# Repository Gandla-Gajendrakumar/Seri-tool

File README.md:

# Seri-tool

Low-cost climate monitor for silkworm rearing sheds in India: temperature and humidity
24×7, SMS alerts in Telugu / Kannada / Hindi / English, thermal-printer log, Wi-Fi / 4G upload,
battery backup. Designed and verified in software before any hardware is bought.

## Layout

| Path | Contents |
|---|---|
| `firmware/` | PlatformIO project. `lib/core` = pure, PC-testable logic. `lib/hal` = hardware interfaces. `test/` = unit tests. |
| `sim/wokwi/` | Wokwi virtual hardware: diagram, custom chips (A7670C, printer, SHT31), scenarios. |
| `sim/replay/` | Whole-rearing-cycle replay data and expected outputs. |
| `hardware/kicad/` | Carrier PCB schematic and layout. |
| `hardware/spice/` | ngspice power-stage simulations. |
| `hardware/power_budget/` | Battery-life calculator. |
| `mechanical/cadquery/` | Enclosure and component models. |
| `bom/` | Bill of materials with Indian suppliers. |
| `docs/` | Requirements, decisions, questions, datasheet facts, evidence; **`docs/handoff/` = the hand-off pack.** |
| `hardware/fab/` | PCB fabrication files (Gerbers zip, schematic, assembly drawing, STEP). |
| `firmware/release/` | Flashable firmware binaries with checksums. |
| `tools/` | Helper scripts (`check_toolchain.sh`). |

## Quick check

```
tools/check_toolchain.sh        # exercises every tool; exit code = failures
cd firmware && pio test -e native
```

## Status

| Phase | State | Evidence |
|---|---|---|
| 0 Setup | Approved 2026-11-21 | `tools/check_toolchain.sh`, `docs/requirements.md` |
| 1 Logic | Approved 2026-11-22 | `tools/phase1_gate.sh` → `docs/evidence/phase1-gate.txt` |
| 2 Firmware on virtual hardware | Approved 2026-11-22 (all 8 Wokwi scenarios) | `docs/evidence/phase2-gate.md` |
| 3 Whole-cycle replay | Approved 2026-11-22 | `tools/phase3_gate.sh` → `docs/evidence/phase3-gate.md` |
| 4 Electronics | Approved 2026-11-22 (re-checked after the Keystone 1043 change) | `tools/phase4_gate.sh` → `docs/evidence/phase4-gate.txt`; `docs/hardware/power-architecture.md` |
| 5 BOM | FINAL 2026-11-22 (D-062: in-stock boost module and modem board) | `tools/phase5_gate.sh` → `bom/bom.md`, `docs/evidence/phase5-gate.txt` |
| 6 Enclosure | Approved 2026-11-22 | `tools/phase6_gate.sh` → `docs/evidence/phase6-gate.txt`, renders in `docs/evidence/phase6/` |
| 7 Hand-off pack | Approved 2026-11-22 | `tools/phase7_gate.sh` → `docs/evidence/phase7-gate.txt`; start at `docs/handoff/README.md` |

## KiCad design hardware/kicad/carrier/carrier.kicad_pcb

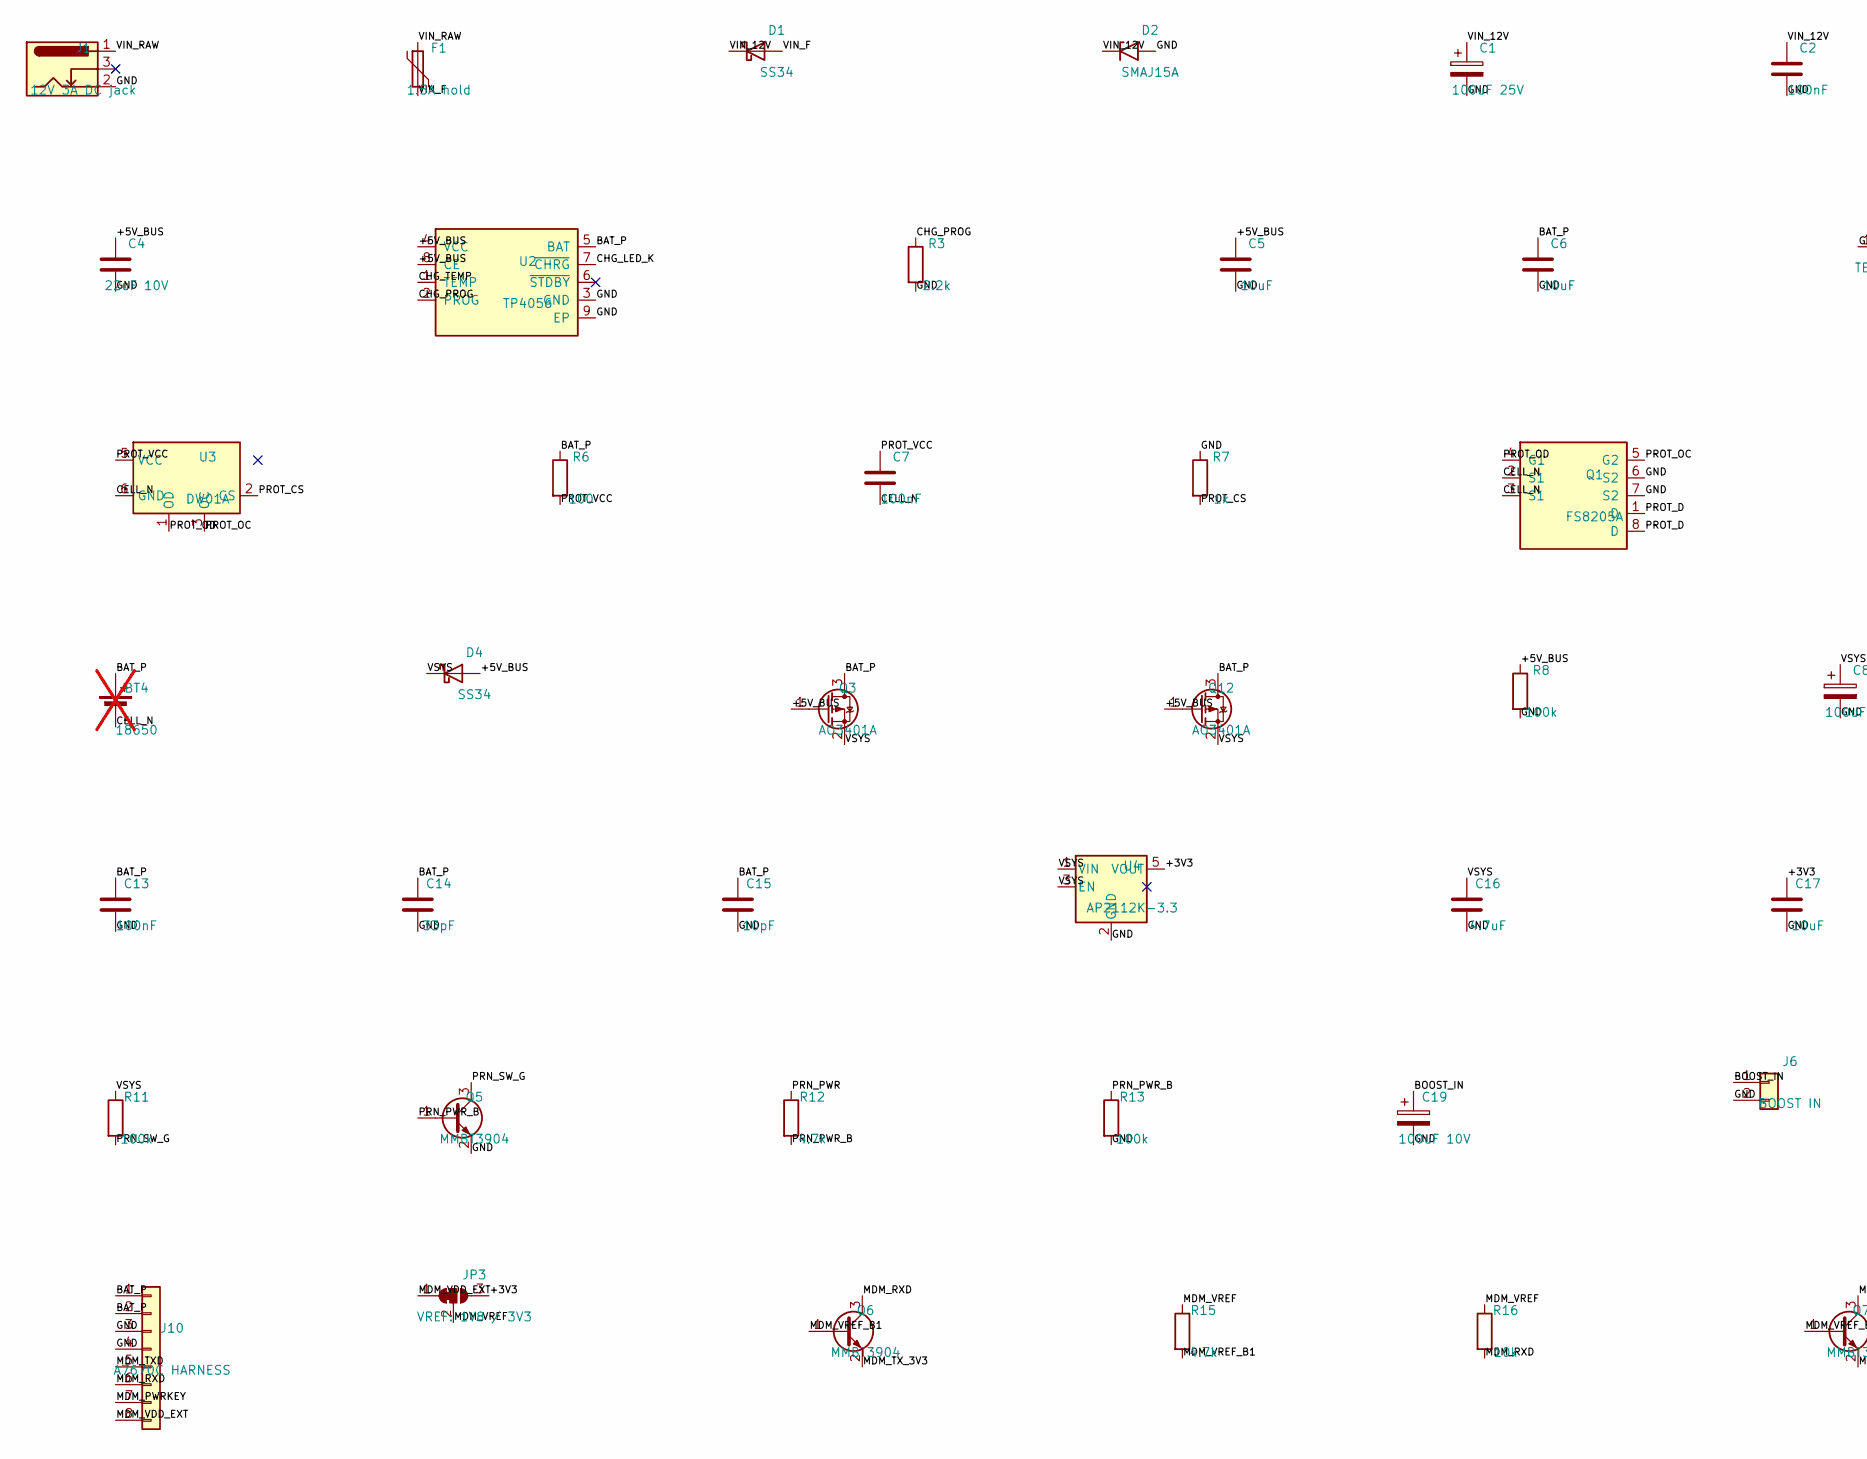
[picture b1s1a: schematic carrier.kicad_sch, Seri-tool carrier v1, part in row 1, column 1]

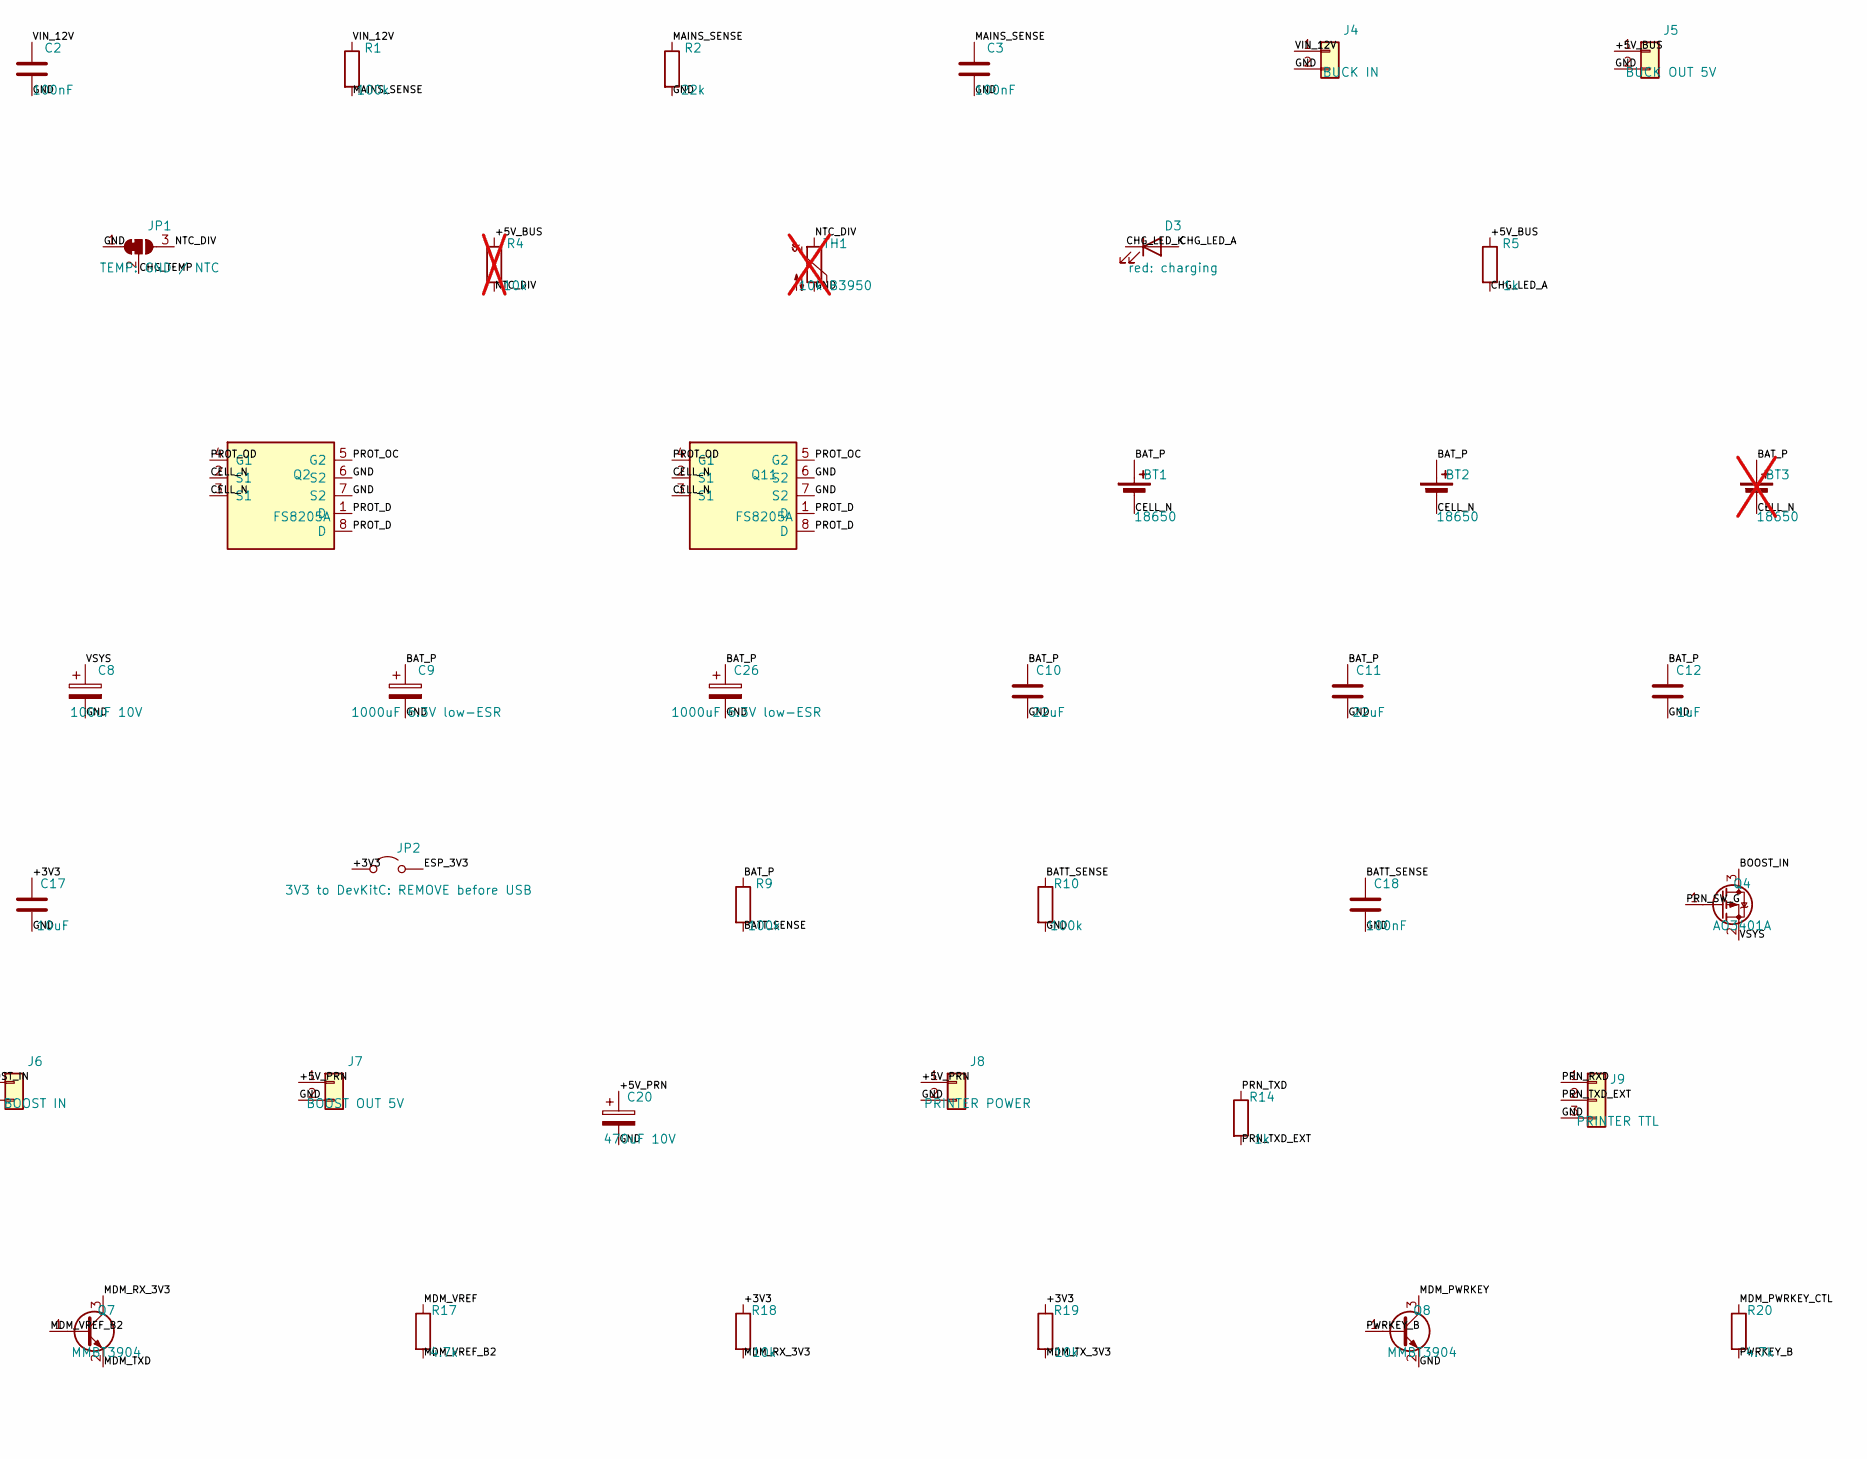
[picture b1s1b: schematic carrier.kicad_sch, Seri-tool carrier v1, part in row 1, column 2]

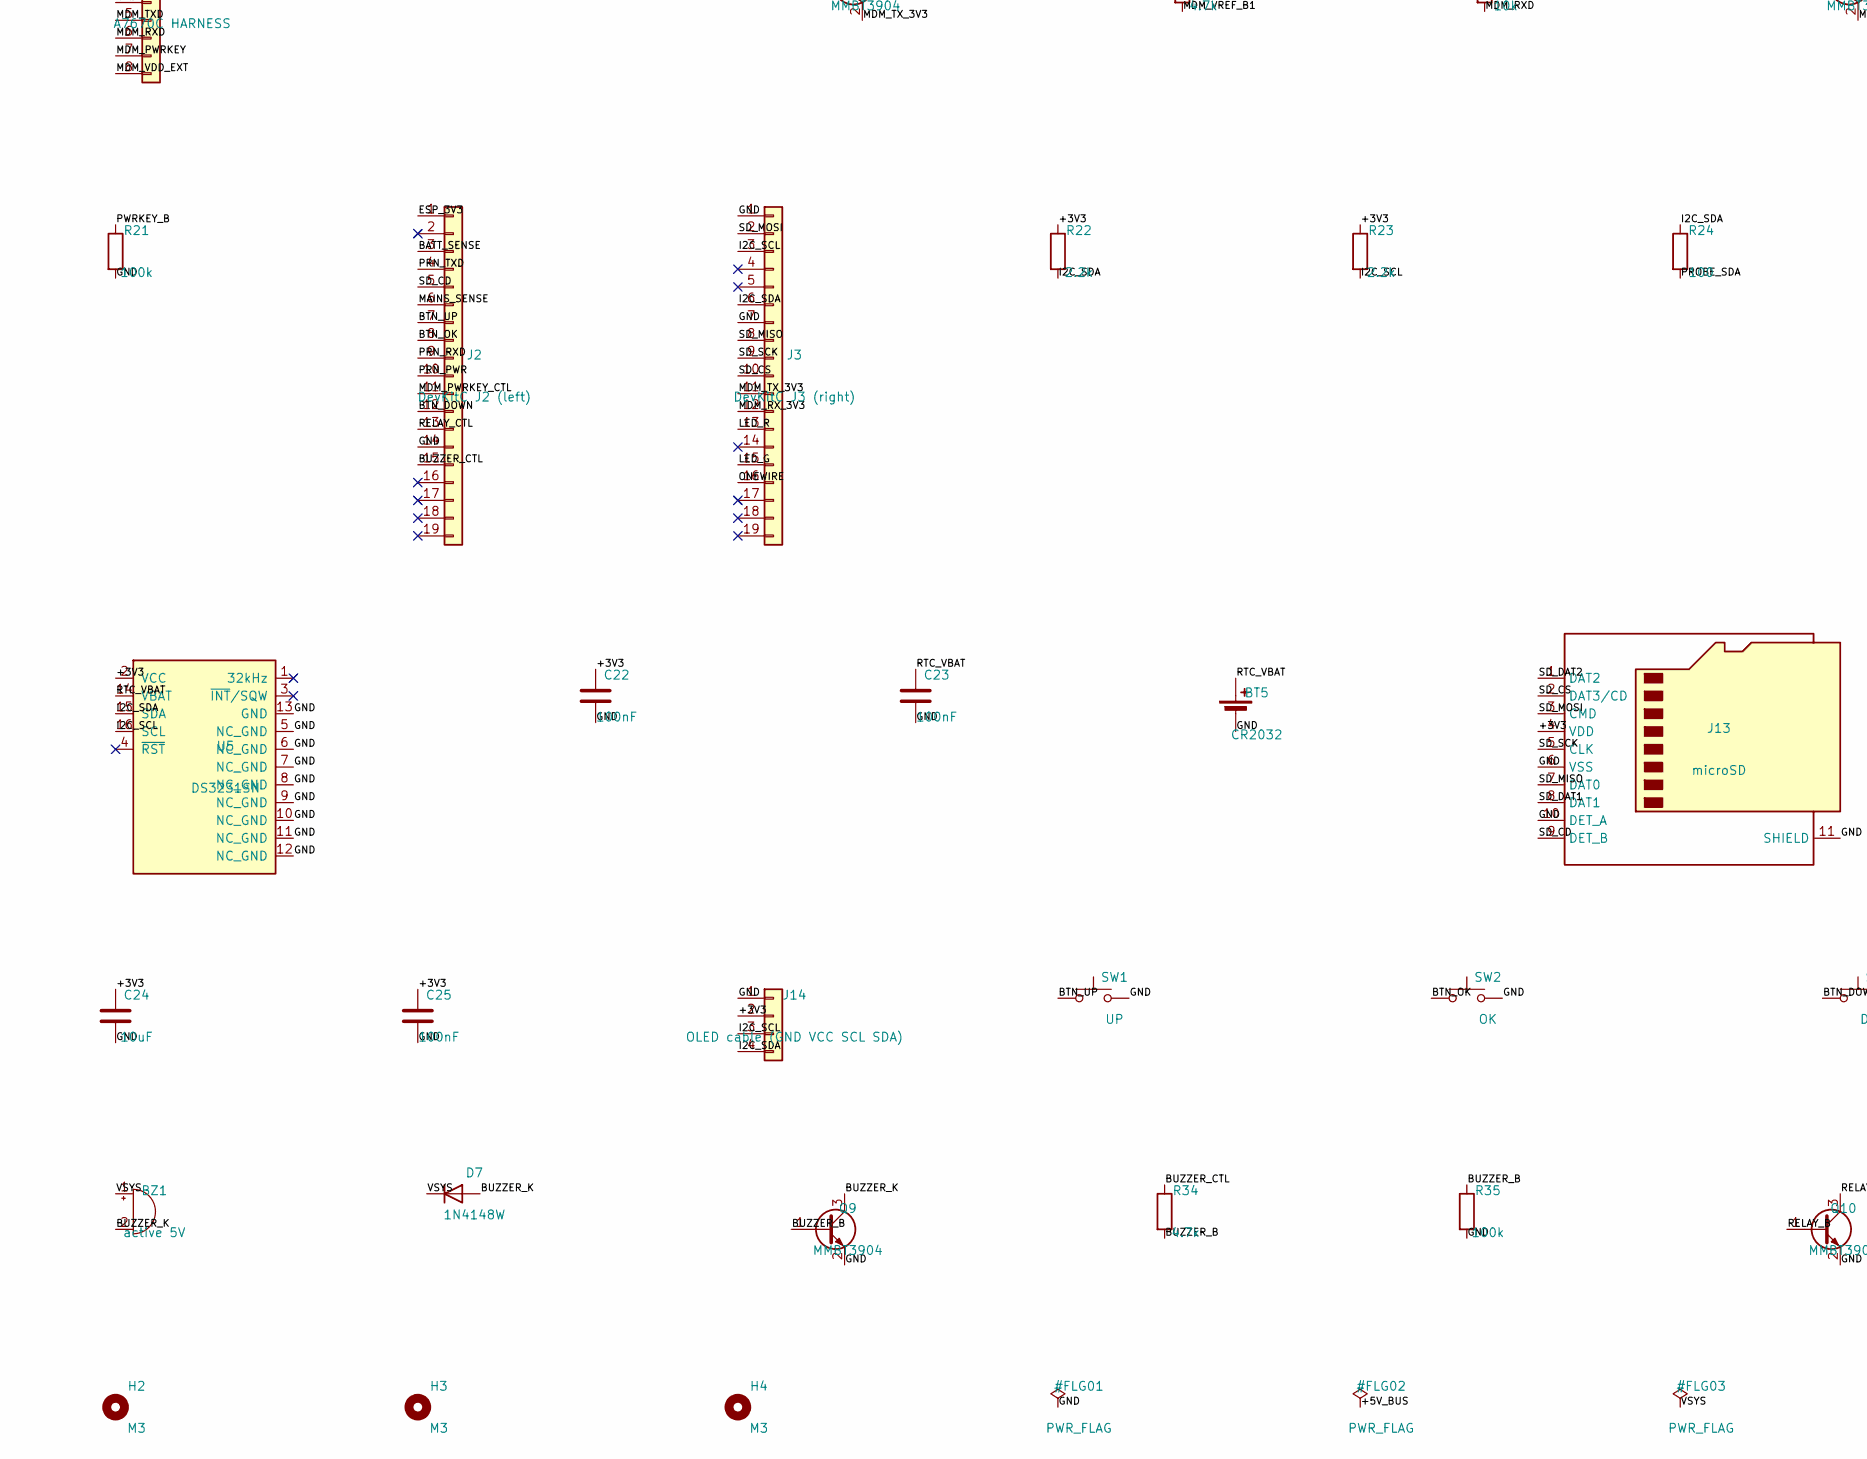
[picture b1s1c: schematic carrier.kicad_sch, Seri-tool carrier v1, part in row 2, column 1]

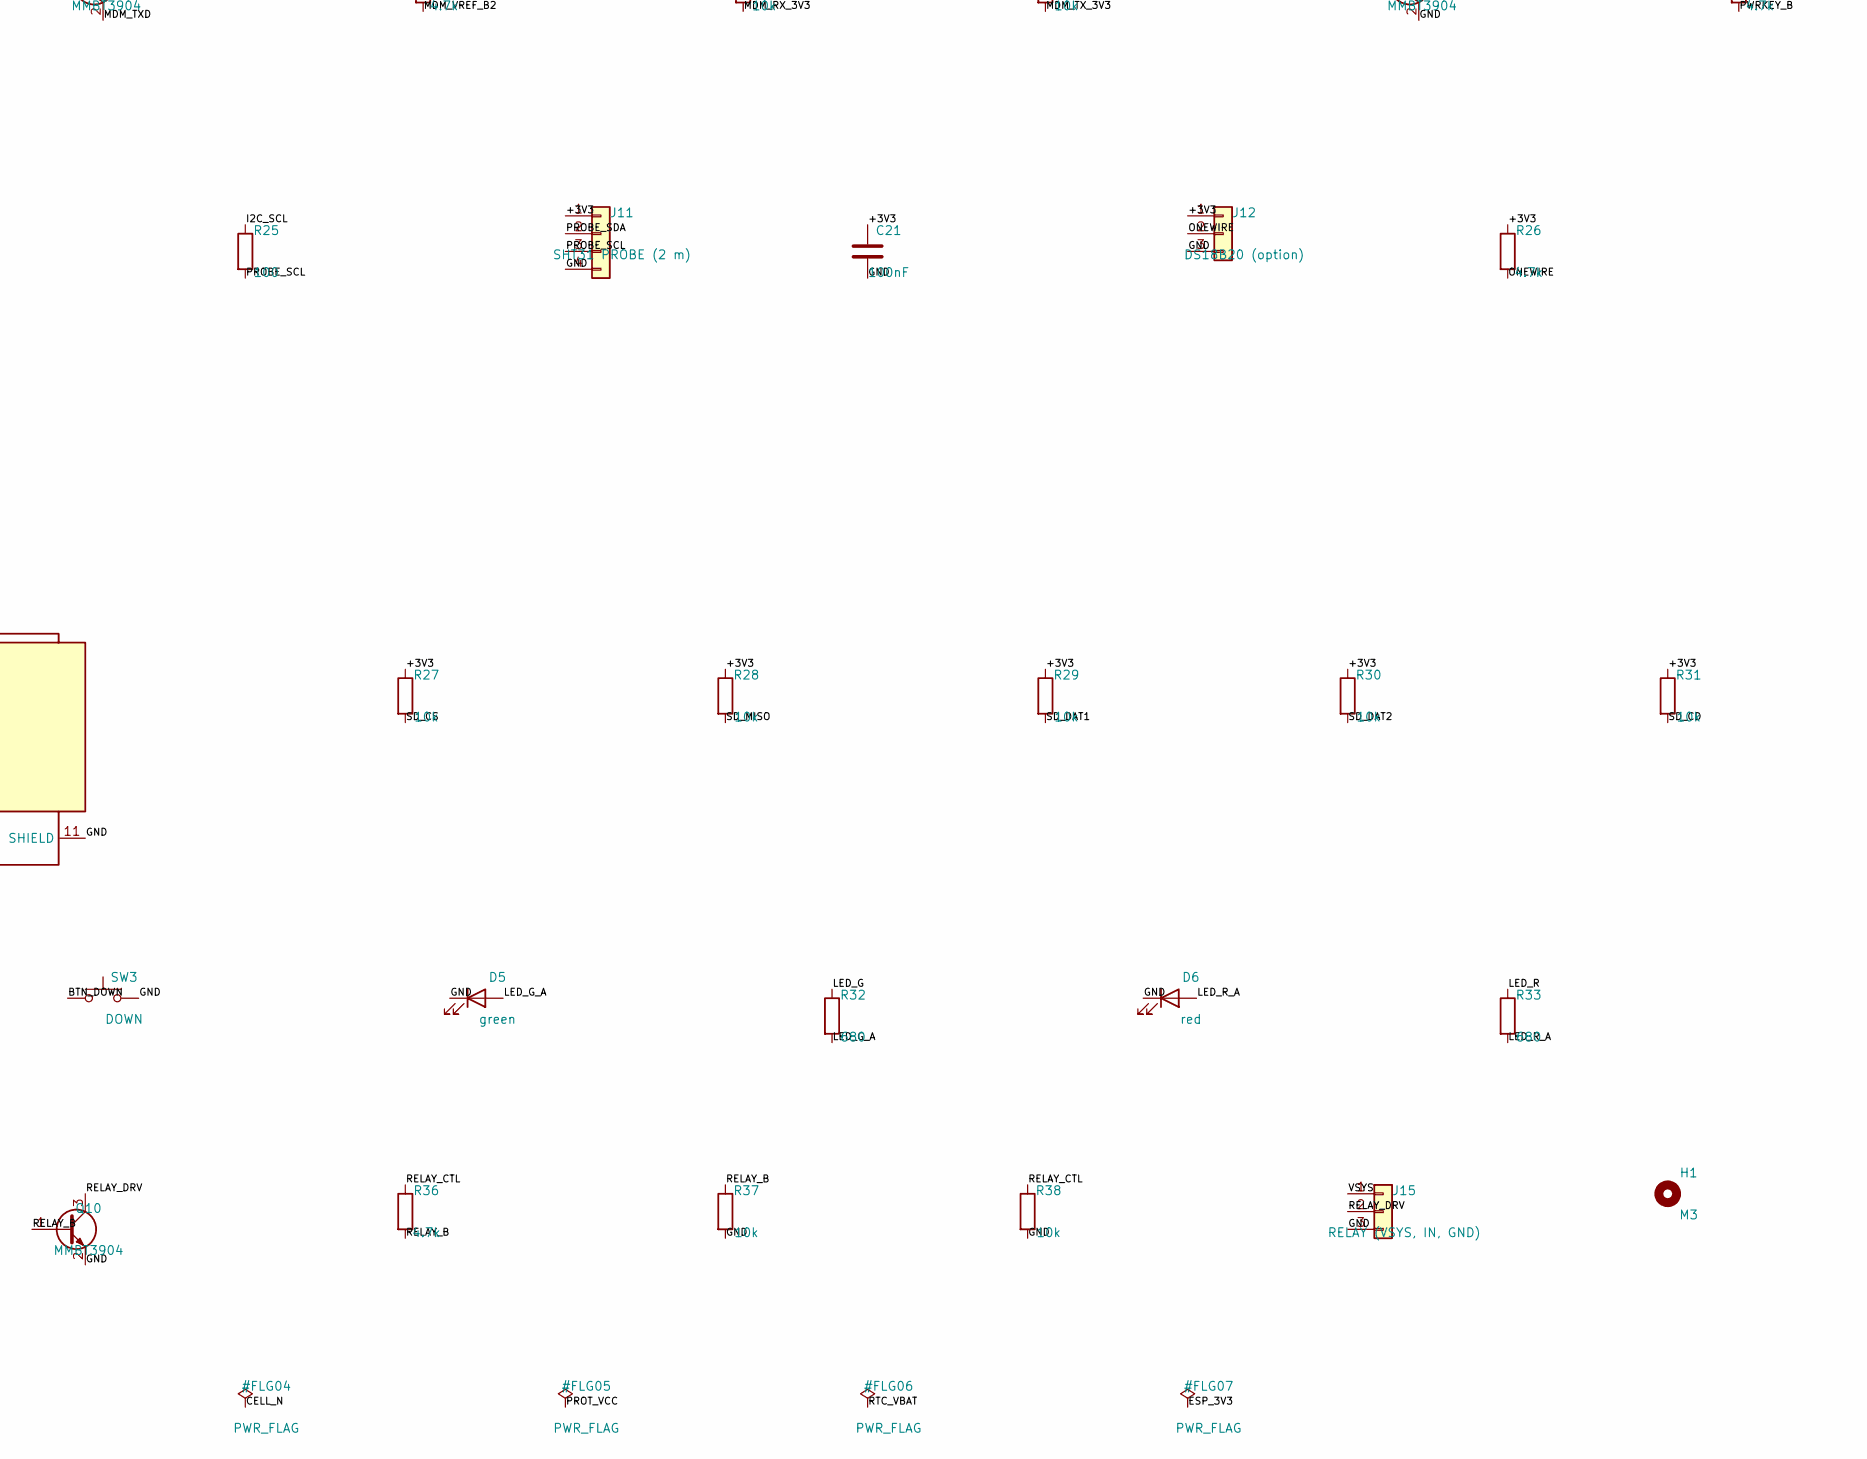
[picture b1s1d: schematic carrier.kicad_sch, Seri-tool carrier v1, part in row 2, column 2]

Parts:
BT1, BT2: 18650; BatteryHolder_Keystone_1043_1x18650
BT3, BT4: 18650; BatteryHolder_Keystone_1043_1x18650; not fitted
BT5: CR2032; BatteryHolder_Keystone_3002_1x2032
BZ1: active 5V; Buzzer_12x9.5RM7.6
C1: 100uF 25V; CP_Radial_D8.0mm_P3.50mm
C2, C3, C7, C13, C18, C21, C22, C23, C25: 100nF; C_0805_2012Metric_Pad1.18x1.45mm_HandSolder
C4: 22uF 10V; C_1206_3216Metric_Pad1.33x1.80mm_HandSolder
C5, C6, C17, C24: 10uF; C_1206_3216Metric_Pad1.33x1.80mm_HandSolder
C8, C19: 100uF 10V; CP_Radial_D6.3mm_P2.50mm
C9, C26: 1000uF 6.3V low-ESR; CP_Radial_D10.0mm_P5.00mm
C10, C11: 22uF; C_1206_3216Metric_Pad1.33x1.80mm_HandSolder
C12: 1uF; C_0805_2012Metric_Pad1.18x1.45mm_HandSolder
C14: 33pF; C_0805_2012Metric_Pad1.18x1.45mm_HandSolder
C15: 10pF; C_0805_2012Metric_Pad1.18x1.45mm_HandSolder
C16: 4.7uF; C_0805_2012Metric_Pad1.18x1.45mm_HandSolder
C20: 470uF 10V; CP_Radial_D8.0mm_P3.50mm
D1, D4: SS34; D_SMA_Handsoldering
D2: SMAJ15A; D_SMA_Handsoldering
D3: red: charging; LED_D3.0mm
D5: green; LED_D3.0mm
D6: red; LED_D3.0mm
D7: 1N4148W; D_SOD-123
F1: 1.5A hold; Fuse_1812_4532Metric_Pad1.30x3.40mm_HandSolder
H1, H2, H3, H4: M3; MountingHole_3.2mm_M3
J1: 12V 3A DC jack; BarrelJack_Horizontal
J2: DevKitC J2 (left); PinSocket_1x19_P2.54mm_Vertical
J3: DevKitC J3 (right); PinSocket_1x19_P2.54mm_Vertical
J4: BUCK IN; PinHeader_1x02_P2.54mm_Vertical
J5: BUCK OUT 5V; PinHeader_1x02_P2.54mm_Vertical
J6: BOOST IN; PinHeader_1x02_P2.54mm_Vertical
J7: BOOST OUT 5V; PinHeader_1x02_P2.54mm_Vertical
J8: PRINTER POWER; JST_XH_B2B-XH-A_1x02_P2.50mm_Vertical
J9: PRINTER TTL; JST_XH_B3B-XH-A_1x03_P2.50mm_Vertical
J10: A7670C HARNESS; PinHeader_1x08_P2.54mm_Vertical
J11: SHT31 PROBE (2 m); JST_XH_B4B-XH-A_1x04_P2.50mm_Vertical
J12: DS18B20 (option); JST_XH_B3B-XH-A_1x03_P2.50mm_Vertical
J13: microSD; microSD_HC_Hirose_DM3AT-SF-PEJM5
J14: OLED cable (GND VCC SCL SDA); PinHeader_1x04_P2.54mm_Vertical
J15: RELAY (VSYS, IN, GND); JST_XH_B3B-XH-A_1x03_P2.50mm_Vertical
JP1: TEMP: GND / NTC; SolderJumper-3_P1.3mm_Bridged12_RoundedPad1.0x1.5mm
JP2: 3V3 to DevKitC: REMOVE before USB; PinHeader_1x02_P2.54mm_Vertical
JP3: VREF: 1V8 / 3V3; SolderJumper-3_P1.3mm_Bridged12_RoundedPad1.0x1.5mm
Q1, Q2, Q11: FS8205A; TSSOP-8_4.4x3mm_P0.65mm
Q3, Q4, Q12: AO3401A; SOT-23
Q5, Q6, Q7, Q8, Q9, Q10: MMBT3904; SOT-23
R1, R8, R9, R10, R11, R13, R21, R35: 100k; R_0805_2012Metric_Pad1.20x1.40mm_HandSolder
R2: 22k; R_0805_2012Metric_Pad1.20x1.40mm_HandSolder
R3, R22, R23: 2.2k; R_0805_2012Metric_Pad1.20x1.40mm_HandSolder
R4: 10k; R_0805_2012Metric_Pad1.20x1.40mm_HandSolder; not fitted
R5, R7, R14: 1k; R_0805_2012Metric_Pad1.20x1.40mm_HandSolder
R6, R24, R25: 100; R_0805_2012Metric_Pad1.20x1.40mm_HandSolder
R12, R15, R17, R20, R26, R34, R36: 4.7k; R_0805_2012Metric_Pad1.20x1.40mm_HandSolder
R16, R18, R19, R27, R28, R29, R30, R31, R37, R38: 10k; R_0805_2012Metric_Pad1.20x1.40mm_HandSolder
R32, R33: 680; R_0805_2012Metric_Pad1.20x1.40mm_HandSolder
SW1: UP; SW_PUSH_6mm_H13mm
SW2: OK; SW_PUSH_6mm_H13mm
SW3: DOWN; SW_PUSH_6mm_H13mm
TH1: 10k B3950; JST_XH_B2B-XH-A_1x02_P2.50mm_Vertical; not fitted
U2: TP4056; SOIC-8-1EP_3.9x4.9mm_P1.27mm_EP2.41x3.3mm
U3: DW01A; SOT-23-6
U4: AP2112K-3.3; SOT-23-5
U5: DS3231SN; SOIC-16W_7.5x10.3mm_P1.27mm

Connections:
/+3V3: C17.1, C21.1, C22.1, C24.1, C25.1, J11.1, J12.1, J13.4 (VDD), J14.2, JP2.1 (A), JP3.3 (B), R18.1, R19.1, R22.1, R23.1, R26.1, R27.1, R28.1, R29.1, R30.1, R31.1, U4.5 (VOUT), U5.2 (VCC)
/+5V_BUS: C4.1, C5.1, D4.2 (A), J5.1, Q3.1 (G), Q12.1 (G), R4.1, R5.1, R8.1, U2.4 (VCC), U2.8 (CE)
/+5V_PRN: C20.1, J7.1, J8.1
/BATT_SENSE: C18.1, J2.3, R9.2, R10.1
/BAT_P: BT1.1 (+), BT2.1 (+), BT3.1 (+), BT4.1 (+), C6.1, C9.1, C10.1, C11.1, C12.1, C13.1, C14.1, C15.1, C26.1, J10.1, J10.2, Q3.3 (D), Q12.3 (D), R6.1, R9.1, U2.5 (BAT)
/BOOST_IN: C19.1, J6.1, Q4.3 (D)
/BTN_DOWN: J2.12, SW3.1
/BTN_OK: J2.8, SW2.1
/BTN_UP: J2.7, SW1.1
/BUZZER_B: Q9.1 (B), R34.2, R35.1
/BUZZER_CTL: J2.15, R34.1
/BUZZER_K: BZ1.2 (-), D7.2 (A), Q9.3 (C)
/CELL_N: BT1.2 (-), BT2.2 (-), BT3.2 (-), BT4.2 (-), C7.2, Q1.2 (S1), Q1.3 (S1), Q2.2 (S1), Q2.3 (S1), Q11.2 (S1), Q11.3 (S1), U3.6 (GND)
/CHG_LED_A: D3.2 (A), R5.2
/CHG_LED_K: D3.1 (K), U2.7 (~CHRG)
/CHG_PROG: R3.1, U2.2 (PROG)
/CHG_TEMP: JP1.2 (C), U2.1 (TEMP)
/ESP_3V3: J2.1, JP2.2 (B)
/GND: BT5.2 (-), C1.2, C2.2, C3.2, C4.2, C5.2, C6.2, C8.2, C9.2, C10.2, C11.2, C12.2, C13.2, C14.2, C15.2, C16.2, C17.2, C18.2, C19.2, C20.2, C21.2, C22.2, C23.2, C24.2, C25.2, C26.2, D2.2 (A2), D5.1 (K), D6.1 (K), J1.2, J2.14, J3.1, J3.7, J4.2, J5.2, J6.2, J7.2, J8.2, J9.3, J10.3, J10.4, J11.4, J12.3, J13.6 (VSS), J13.10 (DET_A), J13.11 (SHIELD), J14.1, J15.3, JP1.1 (A), Q1.6 (S2), Q1.7 (S2), Q2.6 (S2), Q2.7 (S2), Q5.2 (E), Q8.2 (E), Q9.2 (E), Q10.2 (E), Q11.6 (S2), Q11.7 (S2), R2.2, R3.2, R7.1, R8.2, R10.2, R13.2, R21.2, R35.2, R37.2, R38.2, SW1.2, SW2.2, SW3.2, TH1.2, U2.3 (GND), U2.9 (EP), U4.2 (GND), U5.5 (NC_GND), U5.6 (NC_GND), U5.7 (NC_GND), U5.8 (NC_GND), U5.9 (NC_GND), U5.10 (NC_GND), U5.11 (NC_GND), U5.12 (NC_GND), U5.13 (GND)
/I2C_SCL: J3.3, J14.3, R23.2, R25.1, U5.16 (SCL)
/I2C_SDA: J3.6, J14.4, R22.2, R24.1, U5.15 (SDA)
/LED_G: J3.15, R32.1
/LED_G_A: D5.2 (A), R32.2
/LED_R: J3.13, R33.1
/LED_R_A: D6.2 (A), R33.2
/MAINS_SENSE: C3.1, J2.6, R1.2, R2.1
/MDM_PWRKEY: J10.7, Q8.3 (C)
/MDM_PWRKEY_CTL: J2.11, R20.1
/MDM_RXD: J10.6, Q6.3 (C), R16.2
/MDM_RX_3V3: J3.12, Q7.3 (C), R18.2
/MDM_TXD: J10.5, Q7.2 (E)
/MDM_TX_3V3: J3.11, Q6.2 (E), R19.2
/MDM_VDD_EXT: J10.8, JP3.1 (A)
/MDM_VREF: JP3.2 (C), R15.1, R16.1, R17.1
/MDM_VREF_B1: Q6.1 (B), R15.2
/MDM_VREF_B2: Q7.1 (B), R17.2
/NTC_DIV: JP1.3 (B), R4.2, TH1.1
/ONEWIRE: J3.16, J12.2, R26.2
/PRN_PWR: J2.10, R12.1
/PRN_PWR_B: Q5.1 (B), R12.2, R13.1
/PRN_RXD: J2.9, J9.1
/PRN_SW_G: Q4.1 (G), Q5.3 (C), R11.2
/PRN_TXD: J2.4, R14.1
/PRN_TXD_EXT: J9.2, R14.2
/PROBE_SCL: J11.3, R25.2
/PROBE_SDA: J11.2, R24.2
/PROT_CS: R7.2, U3.2 (CS)
/PROT_D: Q1.1 (D), Q1.8 (D), Q2.1 (D), Q2.8 (D), Q11.1 (D), Q11.8 (D)
/PROT_OC: Q1.5 (G2), Q2.5 (G2), Q11.5 (G2), U3.3 (OC)
/PROT_OD: Q1.4 (G1), Q2.4 (G1), Q11.4 (G1), U3.1 (OD)
/PROT_VCC: C7.1, R6.2, U3.5 (VCC)
/PWRKEY_B: Q8.1 (B), R20.2, R21.1
/RELAY_B: Q10.1 (B), R36.2, R37.1
/RELAY_CTL: J2.13, R36.1, R38.1
/RELAY_DRV: J15.2, Q10.3 (C)
/RTC_VBAT: BT5.1 (+), C23.1, U5.14 (VBAT)
/SD_CD: J2.5, J13.9 (DET_B), R31.2
/SD_CS: J3.10, J13.2 (DAT3/CD), R27.2
/SD_DAT1: J13.8 (DAT1), R29.2
/SD_DAT2: J13.1 (DAT2), R30.2
/SD_MISO: J3.8, J13.7 (DAT0), R28.2
/SD_MOSI: J3.2, J13.3 (CMD)
/SD_SCK: J3.9, J13.5 (CLK)
/VIN_12V: C1.1, C2.1, D1.1 (K), D2.1 (A1), J4.1, R1.1
/VIN_F: D1.2 (A), F1.2
/VIN_RAW: F1.1, J1.1
/VSYS: BZ1.1 (+), C8.1, C16.1, D4.1 (K), D7.1 (K), J15.1, Q3.2 (S), Q4.2 (S), Q12.2 (S), R11.1, U4.1 (VIN), U4.3 (EN)

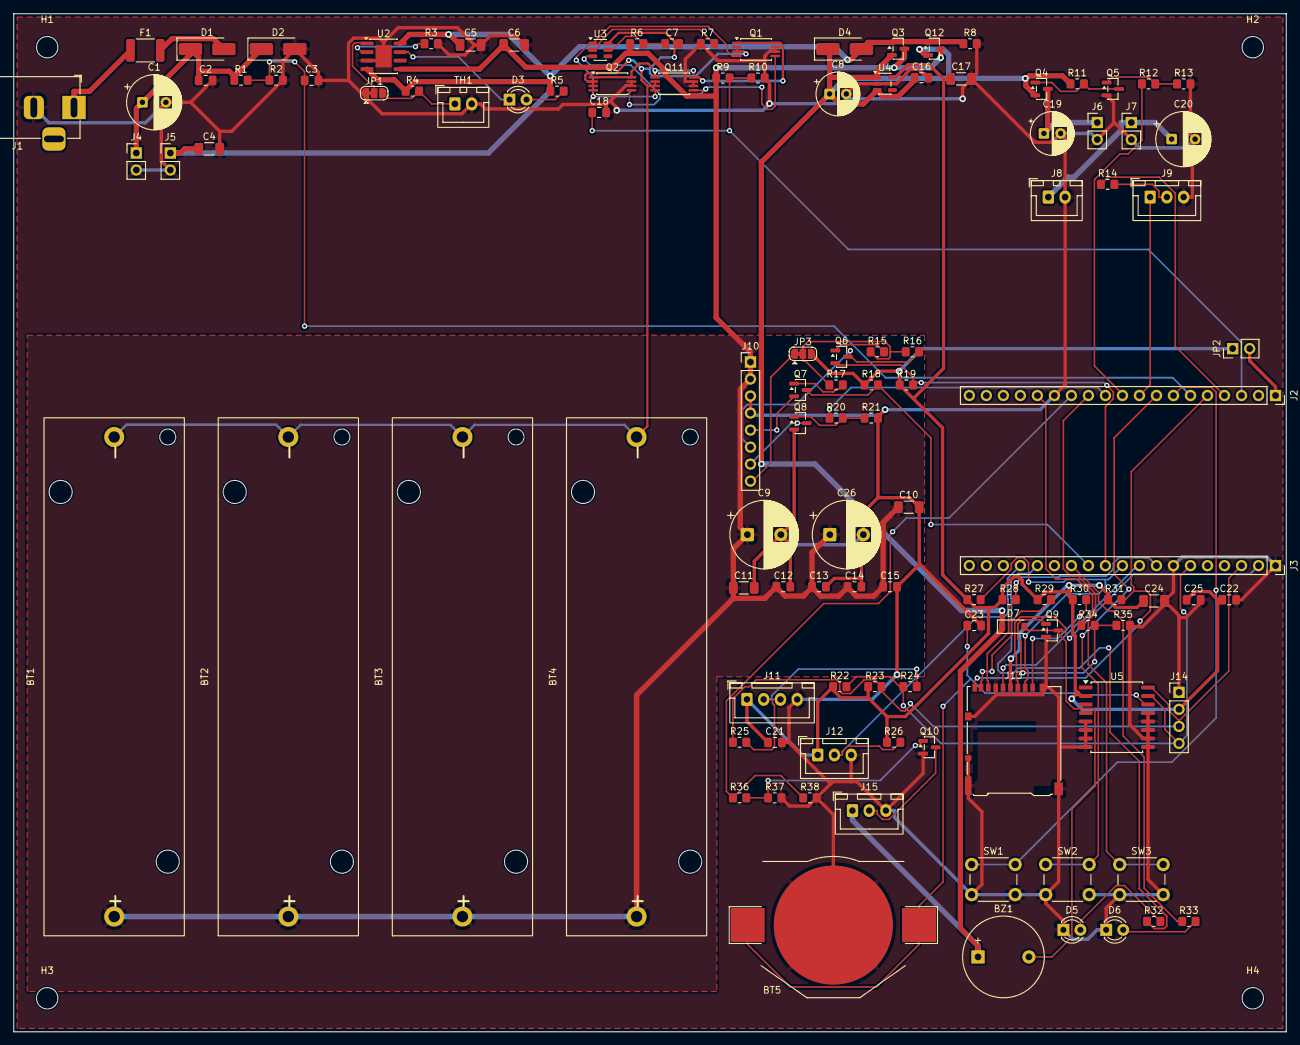
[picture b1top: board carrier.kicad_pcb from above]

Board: 2 copper layers, 190.0 x 152.0 mm, 120 parts (0 on the bottom side), 67 nets.

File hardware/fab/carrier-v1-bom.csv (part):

item,value,qty,refs,dnp_refs,footprint,manufacturer,mpn,supplier,url,unit_inr,line_inr,batch10_inr
"DC barrel jack 5.5x2.1 mm, PCB horizontal with switch pin",12V 3A DC jack,1,J1,,BarrelJack_Horizontal,generic,DC-005,Robu.in,https://aws.robu.in/?p=121507,9.00,9.00,90.00
Polyfuse 1.5 A hold [1812],1.5A hold,1,F1,,Fuse_1812_4532Metric_Pad1.30x3.40mm_HandSolder,Yageo / PTTC (Polytronics),SMD1812B150TF/24 (Yageo) / SMD1812P150TF/24 (PTTC),Evelta,https://evelta.com/resettable-fuse-ptc-24v-1-5a-1812-smd1812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,13.00,13.00,130.00
SS34 [SMA / DO-214AC],SS34,2,D1 D4,,D_SMA_Handsoldering,generic / MDD,SS34,Evelta,https://evelta.com/ss34-sma-40v-3a-schottky-rectifier-diode-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,5.00,10.00,100.00
SMAJ15A [SMA],SMAJ15A,1,D2,,D_SMA_Handsoldering,generic / Jingdao (LCSC),SMAJ15A,Evelta,https://evelta.com/smaj15a-15v-400w-esd-suppressor-tvs-diode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,5.64,5.64,56.40
"Electrolytic 100uF 25V radial 8 mm, 3.5 mm pitch",100uF 25V,1,C1,,CP_Radial_D8.0mm_P3.50mm,generic / Rubycon,"generic; LCSC alt Rubycon 25YXJ100M5X11 (C108360, D5 mm)",Quartz Components,https://quartzcomponents.com/products/100uf-25v-radial-elect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,3.00,3.00,30.00
Capacitor 0805 X7R 100nF 50V,100nF,9,C2 C3 C7 C13 C18 C21 C22 C23 C25,,C_0805_2012Metric_Pad1.18x1.45mm_HandSolder,Walsin / YAGEO,"0805B104K500CT (Walsin) / CC0805KRX7R9BB104 (Yageo, LCSC C49678)",Hubtronics,https://hubtronics.in/walsin-0805b104k500ct,0.49,4.41,49.00
Resistor 0805 1% (per value),100k,8,R1 R8 R9 R10 R11 R13 R21 R35,,R_0805_2012Metric_Pad1.20x1.40mm_HandSolder,generic / UNI-ROYAL (LCSC),0805W8F1002T5E (10k; LCSC C17414) - series 0805W8F____T5E for the other values,Quartz Components (assortment kit),https://quartzcomponents.com/products/30-sets-resistor-kit-8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,0.37,2.93,366.00
Resistor 0805 1% (per value),22k,1,R2,,R_0805_2012Metric_Pad1.20x1.40mm_HandSolder,generic / UNI-ROYAL (LCSC),0805W8F1002T5E (10k; LCSC C17414) - series 0805W8F____T5E for the other values,Quartz Components (assortment kit),https://quartzcomponents.com/products/30-sets-resistor-kit-8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,0.37,0.37,366.00
Male header strip 1x40 2.54 mm + jumper shunt,BUCK IN,1,J4,,PinHeader_1x02_P2.54mm_Vertical,generic,generic,Hubtronics,https://hubtronics.in/misc-connectors/1752,2.95,2.95,29.50
Male header strip 1x40 2.54 mm + jumper shunt,BUCK OUT 5V,1,J5,,PinHeader_1x02_P2.54mm_Vertical,generic,generic,Hubtronics,https://hubtronics.in/misc-connectors/1752,2.95,2.95,29.50
Capacitor 1206 X5R 22uF 10V,22uF 10V,1,C4,,C_1206_3216Metric_Pad1.33x1.80mm_HandSolder,Murata / Samsung,"GRM31CR71A226KE15L (Murata 10V X7R) / CL31A226KAHNNNE (Samsung 25V X5R, LCSC C12891)",Lion Circuits,https://lioncircuits.com/parts/GRM31CR71A226KE15L,35.57,35.57,426.80
"TP4056 [SOP-8 with exposed pad, ESOP-8]",TP4056,1,U2,,SOIC-8-1EP_3.9x4.9mm_P1.27mm_EP2.41x3.3mm,UMW / TOP POWER ASIC (clone families of NanJing Top Power TP4056),TP4056 (UMW) / TP4056-42-ESOP8 (Top Power),Evelta,https://evelta.com/tp4056-1a-linear-lithium-ion-battery-char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,13.05,13.05,130.50
Resistor 0805 1% (per value),2.2k,3,R3 R22 R23,,R_0805_2012Metric_Pad1.20x1.40mm_HandSolder,generic / UNI-ROYAL (LCSC),0805W8F1002T5E (10k; LCSC C17414) - series 0805W8F____T5E for the other values,Quartz Components (assortment kit),https://quartzcomponents.com/products/30-sets-resistor-kit-8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,0.37,1.10,366.00
Capacitor 1206 X5R 10uF 16V,10uF,4,C5 C6 C17 C24,,C_1206_3216Metric_Pad1.33x1.80mm_HandSolder,Samsung,"CL31A106KBHNNNE (50V X5R, LCSC C13585)",LCSC,https://www.lcsc.com/product-detail/C13585.html,10.15,40.62,406.20
Resistor 0805 1% (per value),10k,10,R16 R18 R19 R27 R28 R29 R30 R31 R37 R38,R4,R_0805_2012Metric_Pad1.20x1.40mm_HandSolder,generic / UNI-ROYAL (LCSC),0805W8F1002T5E (10k; LCSC C17414) - series 0805W8F____T5E for the other values,Quartz Components (assortment kit),https://quartzcomponents.com/products/30-sets-resistor-kit-8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,0.37,3.66,366.00
"JST XH 2.54/2.50 mm headers + housings + crimp (2, 3, 4 pin)",10k B3950,0,,TH1,JST_XH_B2B-XH-A_1x02_P2.50mm_Vertical,JST (genuine) / generic XH-compatible,"B2B-XH-A(LF)(SN), B3B-XH-A(LF)(SN), B4B-XH-A(LF)(SN)",Lion Circuits,https://lioncircuits.com/parts/B2B-XH-A,,,
"LED 3 mm red / green, THT",red: charging,1,D3,,LED_D3.0mm,generic / Everlight,3 mm LED red; 3 mm LED green,Electroncomponents,https://www.electroncomponents.com/LED-3mm-Red-Diffused,0.80,0.80,8.00
Resistor 0805 1% (per value),1k,3,R5 R7 R14,,R_0805_2012Metric_Pad1.20x1.40mm_HandSolder,generic / UNI-ROYAL (LCSC),0805W8F1002T5E (10k; LCSC C17414) - series 0805W8F____T5E for the other values,Quartz Components (assortment kit),https://quartzcomponents.com/products/30-sets-resistor-kit-8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,0.37,1.10,366.00
DW01A [SOT-23-6],DW01A,1,U3,,SOT-23-6,PUOLOP (LCSC) / Slkor (DigiKey),DW01A,LCSC,https://www.lcsc.com/product-detail/C351410.html,2.10,2.10,21.00
Resistor 0805 1% (per value),100,3,R6 R24 R25,,R_0805_2012Metric_Pad1.20x1.40mm_HandSolder,generic / UNI-ROYAL (LCSC),0805W8F1002T5E (10k; LCSC C17414) - series 0805W8F____T5E for the other values,Quartz Components (assortment kit),https://quartzcomponents.com/products/30-sets-resistor-kit-8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,0.37,1.10,366.00
FS8205A [TSSOP-8],FS8205A,3,Q1 Q2 Q11,,TSSOP-8_4.4x3mm_P0.65mm,Fortune Semicon / generic 8205A,FS8205A (TSSOP-8),Hubtronics,https://hubtronics.in/8205a-tssop8?tag=FS8205A,5.90,17.70,177.00
"18650 PCB holder, single cell, THT [Keystone 1043]",18650,2,BT1 BT2,BT3 BT4,BatteryHolder_Keystone_1043_1x18650,Keystone Electronics,1043,DigiKey India,https://www.digikey.in/en/products/detail/keystone-electroni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,278.00,556.00,5560.00
AO3401A [SOT-23],AO3401A,3,Q3 Q12 Q4,,SOT-23,Alpha & Omega Semiconductor,AO3401A,LCSC,https://www.lcsc.com/product-detail/C15127.html,6.95,20.85,208.50
"Electrolytic 100uF 10V radial 6.3 mm, 2.5 mm pitch",100uF 10V,2,C8 C19,,CP_Radial_D6.3mm_P2.50mm,Panasonic / generic,"ECE-A1AKA101 (Panasonic KA, 6.3 x 7 mm, 2.5 mm)",Robu.in,https://robu.in/product/100-uf-10v-through-hole-electrolytic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,1.95,3.90,39.00
"Electrolytic 1000uF 6.3V LOW-ESR radial 10 mm, 5 mm pitch",1000uF 6.3V low-ESR,2,C9 C26,,CP_Radial_D10.0mm_P5.00mm,Rubycon / Panasonic,"10ZLH1000MEFC10X12.5 (Rubycon ZLH, 10 V) or EEU-FM0J102 (Panasonic FM, 6.3 V)",Tanotis,https://www.tanotis.com/products/rubycon-10zlh1000mefc10x12-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,71.31,142.62,1426.20
Capacitor 1206 X5R 22uF 10V,22uF,2,C10 C11,,C_1206_3216Metric_Pad1.33x1.80mm_HandSolder,Murata / Samsung,"GRM31CR71A226KE15L (Murata 10V X7R) / CL31A226KAHNNNE (Samsung 25V X5R, LCSC C12891)",Lion Circuits,https://lioncircuits.com/parts/GRM31CR71A226KE15L,35.57,71.13,746.90
Capacitor 0805 X5R/X7R 1uF 25V,1uF,1,C12,,C_0805_2012Metric_Pad1.18x1.45mm_HandSolder,Samsung / Yageo,"CL21B105KAFNFNE (Samsung, LCSC C1712) / CC0805KKX7R8BB105 (Yageo)",LCSC,https://www.lcsc.com/product-detail/C1712.html,2.64,2.64,52.80
Capacitor 0805 C0G 33pF and 10pF,33pF,1,C14,,C_0805_2012Metric_Pad1.18x1.45mm_HandSolder,Vishay / Samsung / generic,"33pF: VJ0805A330JXACW1BC (Vishay) or CL21C330JBANNNC (Samsung, LCSC C1814); 10pF: CL21C100JBANNNC (Samsung, LCSC C1785)",Lion Circuits,https://lioncircuits.com/parts/VJ0805A330JXACW1BC,11.56,11.56,115.60
Capacitor 0805 C0G 33pF and 10pF,10pF,1,C15,,C_0805_2012Metric_Pad1.18x1.45mm_HandSolder,Vishay / Samsung / generic,"33pF: VJ0805A330JXACW1BC (Vishay) or CL21C330JBANNNC (Samsung, LCSC C1814); 10pF: CL21C100JBANNNC (Samsung, LCSC C1785)",Lion Circuits,https://lioncircuits.com/parts/VJ0805A330JXACW1BC,11.56,11.56,115.60
AP2112K-3.3 [SOT-23-5],AP2112K-3.3,1,U4,,SOT-23-5,Diodes Incorporated,AP2112K-3.3TRG1,LCSC,https://www.lcsc.com/product-detail/C51118.html,14.14,14.14,141.40
Capacitor 0805 X5R 4.7uF 10V,4.7uF,1,C16,,C_0805_2012Metric_Pad1.18x1.45mm_HandSolder,Samsung,"CL21A475KAQNNNE (25V X5R, LCSC C1779)",LCSC,https://www.lcsc.com/product-detail/C1779.html,2.91,2.91,58.10
Male header strip 1x40 2.54 mm + jumper shunt,3V3 to DevKitC: REMOVE before USB,1,JP2,,PinHeader_1x02_P2.54mm_Vertical,generic,generic,Hubtronics,https://hubtronics.in/misc-connectors/1752,2.95,2.95,29.50
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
